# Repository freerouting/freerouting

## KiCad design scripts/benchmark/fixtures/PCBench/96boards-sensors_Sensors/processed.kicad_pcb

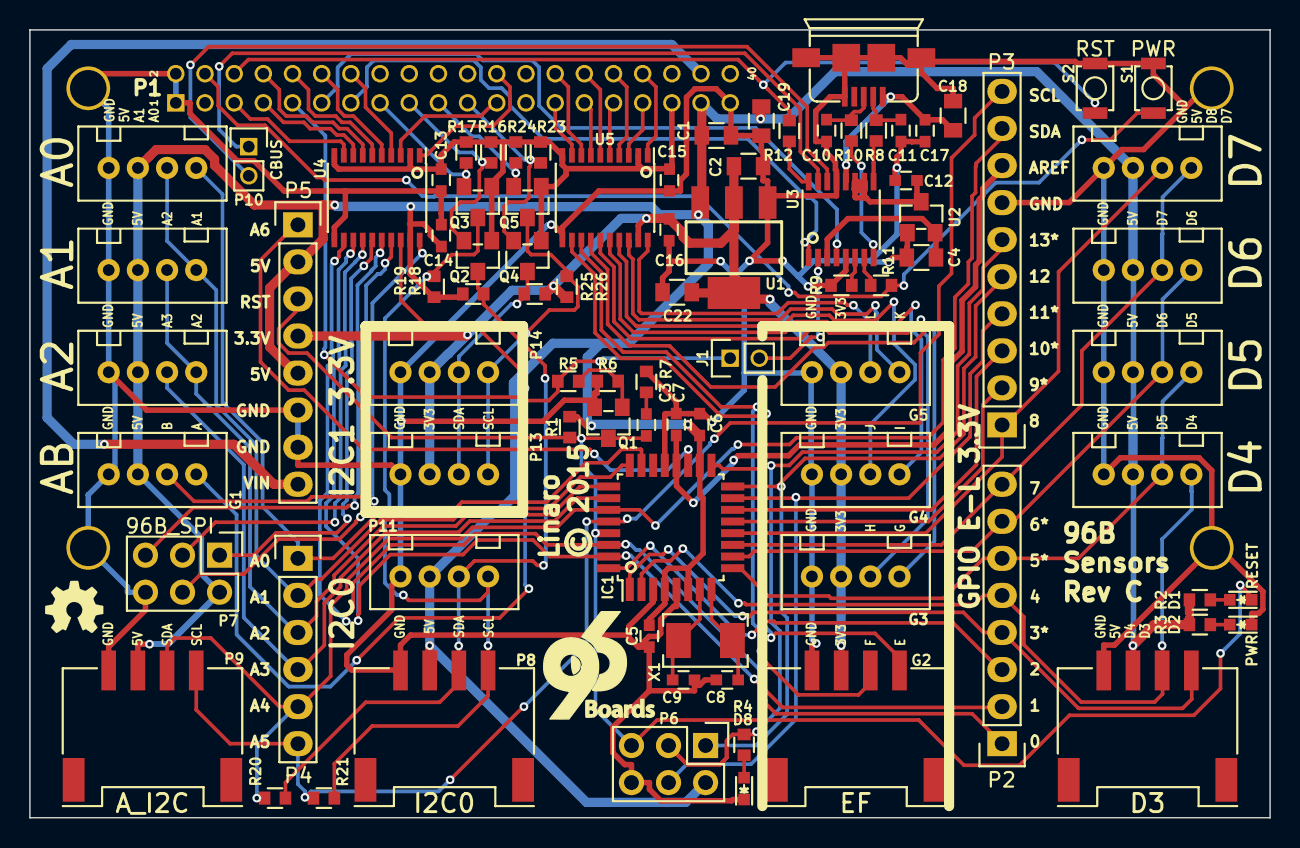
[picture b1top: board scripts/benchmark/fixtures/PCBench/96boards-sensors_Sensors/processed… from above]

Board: 2 copper layers, 85.0 x 54.0 mm, 87 parts (0 on the bottom side), 91 nets.

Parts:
A0, A1, A2: GROVE; Grove4P
C1, C2, C4: 2u2; C_0805
C3, C5, C6, C7, C12, C13, C14, C15, C16, C17: 100n; C_0603
C8, C9: 22p; C_0603
C10, C11: 39p; C_0603
C18, C19, C22: 10u; C_0805
CON1: CONSOLE; USB_MICRO_B_ST-USB-001E
D1: RESET; LED-0603
D2: PWR; LED-0603
D3: GROVE; Grove_SMD_Connector
D4, D5, D6, D7: GROVE; Grove4P
D8: PB5; LED-0603
G1: AB; Grove4P
G2: EF; Grove_SMD_Connector
G3: GH; Grove4P
G4: IJ; Grove4P
G5: KL; Grove4P
IC1: ATMEGA328P; TQFP-32_7x7mm_Pitch0.8mm
J1: RST_TEST; Pin_Header_Straight_1x02_Pitch2mm
P1: CONN_02X20; 96Boards_LS_EXP
P2, P5: CONN_01X08; Socket_Strip_Straight_1x08
P3: CONN_01X10; Socket_Strip_Straight_1x10
P4: CONN_01X06; Socket_Strip_Straight_1x06
P6: AVR_SPI; Pin_Header_Straight_2x03
P7: 96B_SPI; Pin_Header_Straight_2x03
P8: I2C0; Grove_SMD_Connector
P9: A_I2C; Grove_SMD_Connector
P10: CBUS; Pin_Header_Straight_1x02_Pitch2mm
P11: I2C0; Grove4P
P13, P14: I2C1; Grove4P
Q1: S8050; SOT-23_Seeed
Q2, Q3, Q4, Q5: BSS138; SOT-23_Seeed
R1, R6, R9, R16, R17, R18, R19, R23, R24, R25, R26: 10K; R_0603_Seeed
R2, R3, R4: 1K; R_0603_Seeed
R5, R7: 620R; R_0603_Seeed
R8, R10: 22R; R_0603_Seeed
R11, R12: 220R; R_0603_Seeed
R20, R21: R; R_0603_Seeed
S1: PWR; SW_PUSH_B3U_1000P
S2: RST; SW_PUSH_B3U_1000P
U1: CJT1117-3.3; SOT223
U2: XC6206; SOT-23_Seeed
U3: FT230XS; SSOP-16_3.9x4.9mm_Pitch0.635mm
U4: TXB0108PW; SSOP-20_4.4x6.5mm_Pitch0.65mm
U5: TXS0108E; SSOP-20_4.4x6.5mm_Pitch0.65mm
X1: 16MHz; Crystal_3.2X5_SMD

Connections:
96UART0_RTS: J1.1, P1.9, R5.2
96UART0_RX: P1.7, U4.8
96UART0_TX: P1.5, U4.9
96UART1_RX: P1.13, U3.1
96UART1_TX: P1.11, U3.4
+1V8: C13.1, C15.1, P1.35, Q2.1, Q3.1, Q4.1, Q5.1, R16.1, R17.1, R23.1, R24.1, U4.2, U4.10, U5.2, U5.10
+1V8F: C4.1, U2.2, U3.3
+3V3: C2.1, C16.1, C22.1, G2.3, G3.3, G4.3, G5.3, P5.4, P13.3, P14.3, R25.1, R26.1, U1.2, U5.19
+3V3F: C12.1, U2.3, U3.10, U3.11
+5V: A0.3, A1.3, A2.3, C1.1, C5.1, C6.1, C14.1, C19.1, D3.3, D4.3, D5.3, D6.3, D7.3, G1.3, IC1.4, IC1.6, IC1.18, P1.37, P5.2, P5.5, P6.2, P7.2, P8.3, P9.3, P11.3, R1.1, R2.1, R3.1, R18.1, R19.1, U1.3, U4.19
/+5F: C17.1, C18.1, CON1.1, U3.12
/USBDM: C11.1, CON1.2, R8.2
/USBDP: C10.1, CON1.3, R10.2
ADC6: IC1.19, P5.1
AREF: C7.1, IC1.20, P3.8
GND: A0.4, A1.4, A2.4, C1.2, C2.2, C4.2, C5.2, C6.2, C7.2, C8.2, C9.2, C10.2, C11.2, C12.2, C13.2, C14.2, C15.2, C16.2, C17.2, C18.2, C19.2, C22.2, CON1.5, CON1.6, CON1.7, CON1.8, CON1.9, D2.1, D3.4, D4.4, D5.4, D6.4, D7.4, D8.1, G1.4, G2.4, G3.4, G4.4, G5.4, IC1.3, IC1.5, IC1.21, P1.1, P1.2, P1.39, P3.7, P5.6, P5.7, P6.6, P7.6, P8.4, P9.4, P11.4, P13.4, P14.4, Q1.2, R6.1, R7.2, R9.1, S1.2, S2.2, U1.1, U2.1, U3.5, U3.13, U4.11, U5.11
GPIO_A: P1.23, U4.3
GPIO_A_5: G1.1, U4.18
GPIO_B: P1.24, U4.1
GPIO_B_5: G1.2, U4.20
GPIO_E: P1.27, U5.9
GPIO_E_3: G2.1, U5.12
GPIO_F: P1.28, U5.8
GPIO_F_3: G2.2, U5.13
GPIO_G: P1.29, U5.7
GPIO_G_3: G3.1, U5.14
GPIO_H: P1.30, U5.6
GPIO_H_3: G3.2, U5.15
GPIO_I: P1.31, U5.5
GPIO_I_3: G4.1, U5.16
GPIO_J: P1.32, U5.4
GPIO_J_3: G4.2, U5.17
GPIO_K: P1.33, U5.3
GPIO_K_3: G5.1, U5.18
GPIO_L: P1.34, U5.1
GPIO_L_3: G5.2, U5.20
I2C0_SCL: P1.15, Q3.2, R17.2
I2C0_SCL_5: P8.1, P11.1, Q3.3, R19.2, R21.2
I2C0_SDA: P1.17, Q2.2, R16.2
I2C0_SDA_5: P8.2, P11.2, Q2.3, R18.2, R20.2
I2C1_SCL: P1.19, Q5.2, R24.2
I2C1_SCL_3: P13.1, P14.1, Q5.3, R26.2
I2C1_SDA: P1.21, Q4.2, R23.2
I2C1_SDA_3: P13.2, P14.2, Q4.3, R25.2
unnamed: C3.2, R7.1
unnamed: C8.1, IC1.8, X1.1
unnamed: C9.1, IC1.7, X1.2
unnamed: D1.2, R2.2
unnamed: D2.2, R3.2
unnamed: D8.2, R4.2
unnamed: P10.1, U3.15
unnamed: P10.2, U3.14
unnamed: Q1.1, R5.1, R6.2
unnamed: R8.1, U3.9
unnamed: R9.2, U3.6
unnamed: R10.1, U3.8
unnamed: R11.2, U3.7
unnamed: R12.2, U3.16
PB0: D7.2, IC1.12, P3.1
PB1: IC1.13, P3.2
PB2: IC1.14, P3.3
PB3_MOSI: IC1.15, P3.4, P6.4
PB4_MISO: IC1.16, P3.5, P6.1
PB5_SCK: IC1.17, P3.6, P6.3, R4.1
PC0: A0.1, IC1.23, P4.1
PC1: A0.2, A1.1, IC1.24, P4.2
PC2: A1.2, A2.1, IC1.25, P4.3
PC3: A2.2, IC1.26, P4.4
PC4_SDA: IC1.27, P3.9, P4.5, P9.2, R20.1
PC5_SCL: IC1.28, P3.10, P4.6, P9.1, R21.1
PD0_RX: IC1.30, P2.1, U4.12
PD1_TX: IC1.31, P2.2, U4.13
PD2_INT0: IC1.32, P2.3
PD3_INT1: D3.1, IC1.1, P2.4
PD4: D3.2, D4.1, IC1.2, P2.5
PD5: D4.2, D5.1, IC1.9, P2.6
PD6: D5.2, D6.1, IC1.10, P2.7
PD7: D6.2, D7.1, IC1.11, P2.8
PWR_BTN: P1.4, R11.1, S1.1
PWR_IN: P1.38, P5.8
RESET: C3.1, D1.1, IC1.29, P5.3, P6.5, Q1.3, R1.2
RST_BTN: P1.6, R12.1, S2.1
SPI0_CS: P1.12, U4.5
SPI0_CS_5: P7.5, U4.16
SPI0_MISO: P1.10, U4.6
SPI0_MISO_5: P7.1, U4.15
SPI0_MOSI: P1.14, U4.4
SPI0_MOSI_5: P7.4, U4.17
SPI0_SCK: P1.8, U4.7
SPI0_SCK_5: P7.3, U4.14
TEST_RESET: J1.2, U3.2

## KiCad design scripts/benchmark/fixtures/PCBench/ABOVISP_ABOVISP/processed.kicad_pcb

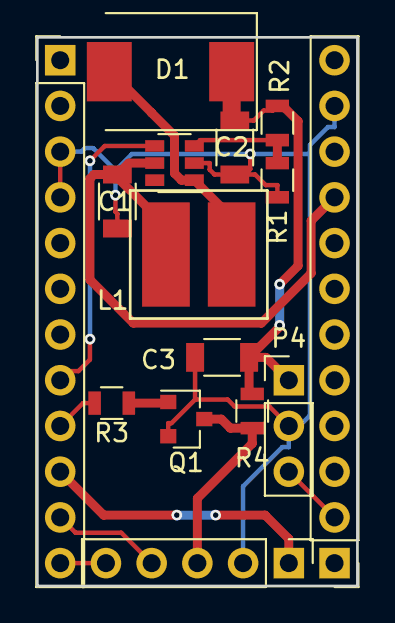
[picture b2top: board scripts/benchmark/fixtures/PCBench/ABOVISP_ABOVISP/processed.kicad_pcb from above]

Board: 2 copper layers, 17.8 x 30.5 mm, 15 parts (0 on the bottom side), 13 nets.

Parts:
C1, C2: 22uF; C_1206
C3: 10uF; C_1206
D1: SS34; D_SMC_Standard
L1: 4.7uH; SMD_Inductor_CD54
P1: CONN_01X05; Socket_Strip_Straight_1x05_Pitch2.54mm
P2, P3: CONN_01X12; Socket_Strip_Straight_1x12_Pitch2.54mm
P4: CONN_01X03; Socket_Strip_Straight_1x03_Pitch2.54mm
Q1: MMBT3904; SOT-23
R1: 2.2K; R_0805
R2: 33K; R_0805
R3: 1K; R_0805
R4: 10K; R_0805
U1: MT3608; SOT-23-6

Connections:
9V: C2.1, C3.1, D1.1, P4.1, R2.2, R4.1
+5V: C1.1, L1.1, P3.9, U1.5
BOOST_EN: P2.8, U1.4
GND: C1.2, C2.2, C3.2, P1.2, P2.3, P2.4, P3.11, P4.2, Q1.2, R1.2, U1.2
GPIO_16: P3.2, P4.3
unnamed: D1.2, L1.2, U1.1
unnamed: Q1.1, R3.1
unnamed: R1.1, R2.1, U1.3
PROG_SCK: P1.4, P2.11
PROG_SDA: P1.5, P2.12
PROG_VCC: P1.1, P2.10
PROG_VPP: P1.3, Q1.3, R4.2
TRIG_VPP: P2.9, R3.2

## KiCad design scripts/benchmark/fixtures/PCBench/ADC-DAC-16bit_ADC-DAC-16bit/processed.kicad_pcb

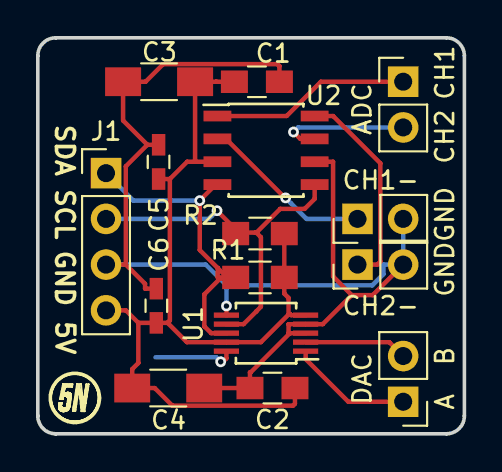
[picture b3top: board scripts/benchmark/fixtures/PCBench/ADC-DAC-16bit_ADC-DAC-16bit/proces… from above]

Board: 2 copper layers, 23.7 x 22.0 mm, 16 parts (1 on the bottom side), 11 nets.

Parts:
C1, C2: 100n; C_0805_HandSoldering
C3, C4: 10u; C_1206_HandSoldering
C5, C6: 100n; C_0603_HandSoldering
J1: CON; Pin_Header_Straight_1x04_Pitch2.54mm
J2: DAC; Pin_Header_Straight_1x02_Pitch2.54mm
J3: ADC; Pin_Header_Straight_1x02_Pitch2.54mm
J4: CH1-; Pin_Header_Straight_1x02_Pitch2.54mm
J5: CH2-; Pin_Header_Straight_1x02_Pitch2.54mm
R1, R2: 4K7; R_0805_HandSoldering
TP1: DAC Vref; Measurement_Point_Round-SMD-Pad_Small
U1: AD5667R; MSOP-10_3x3mm_Pitch0.5mm
U2: MCP3426; SOIC-8_3.9x4.9mm_Pitch1.27mm

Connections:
+5V: C1.1, C2.1, C3.1, C4.1, C5.1, C6.1, J1.4, R1.1, R2.1, U1.5, U1.9, U2.3
GND: C1.2, C2.2, C3.2, C4.2, C5.2, C6.2, J1.3, J4.2, J5.2, U1.3, U1.4, U1.6, U2.6
unnamed: J1.1, R1.2, U1.8, U2.4
unnamed: J1.2, R2.2, U1.7, U2.5
unnamed: J2.1, U1.1
unnamed: J2.2, U1.2
unnamed: J3.1, U2.1
unnamed: J3.2, U2.7
unnamed: J4.1, U2.2
unnamed: J5.1, U2.8
unnamed: TP1.1, U1.10

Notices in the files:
scripts/benchmark/fixtures/PCBench/96boards-sensors_Sensors/processed.kicad_pcb:
© 2015
